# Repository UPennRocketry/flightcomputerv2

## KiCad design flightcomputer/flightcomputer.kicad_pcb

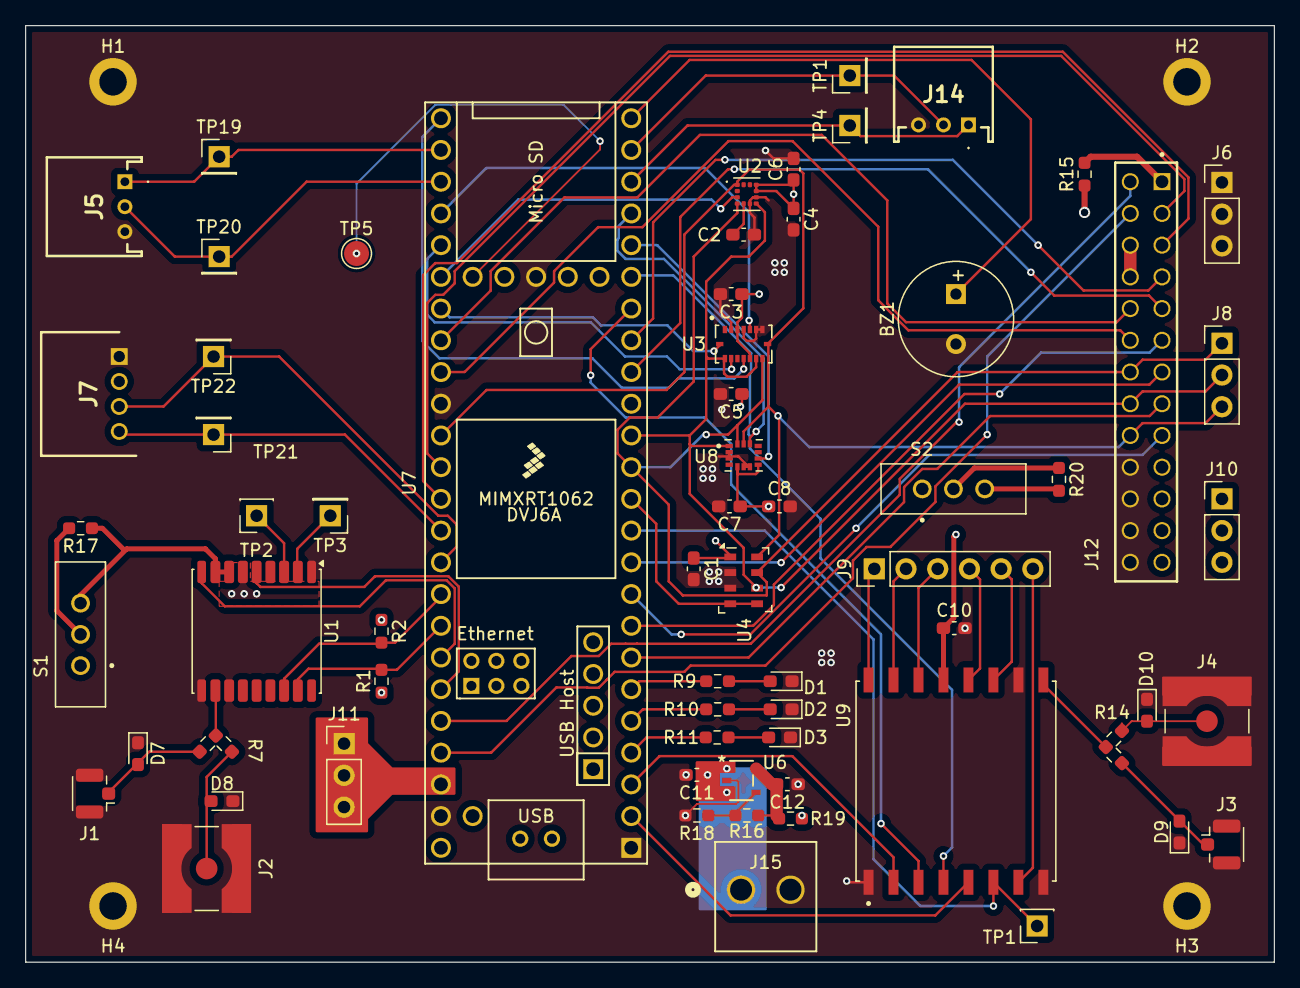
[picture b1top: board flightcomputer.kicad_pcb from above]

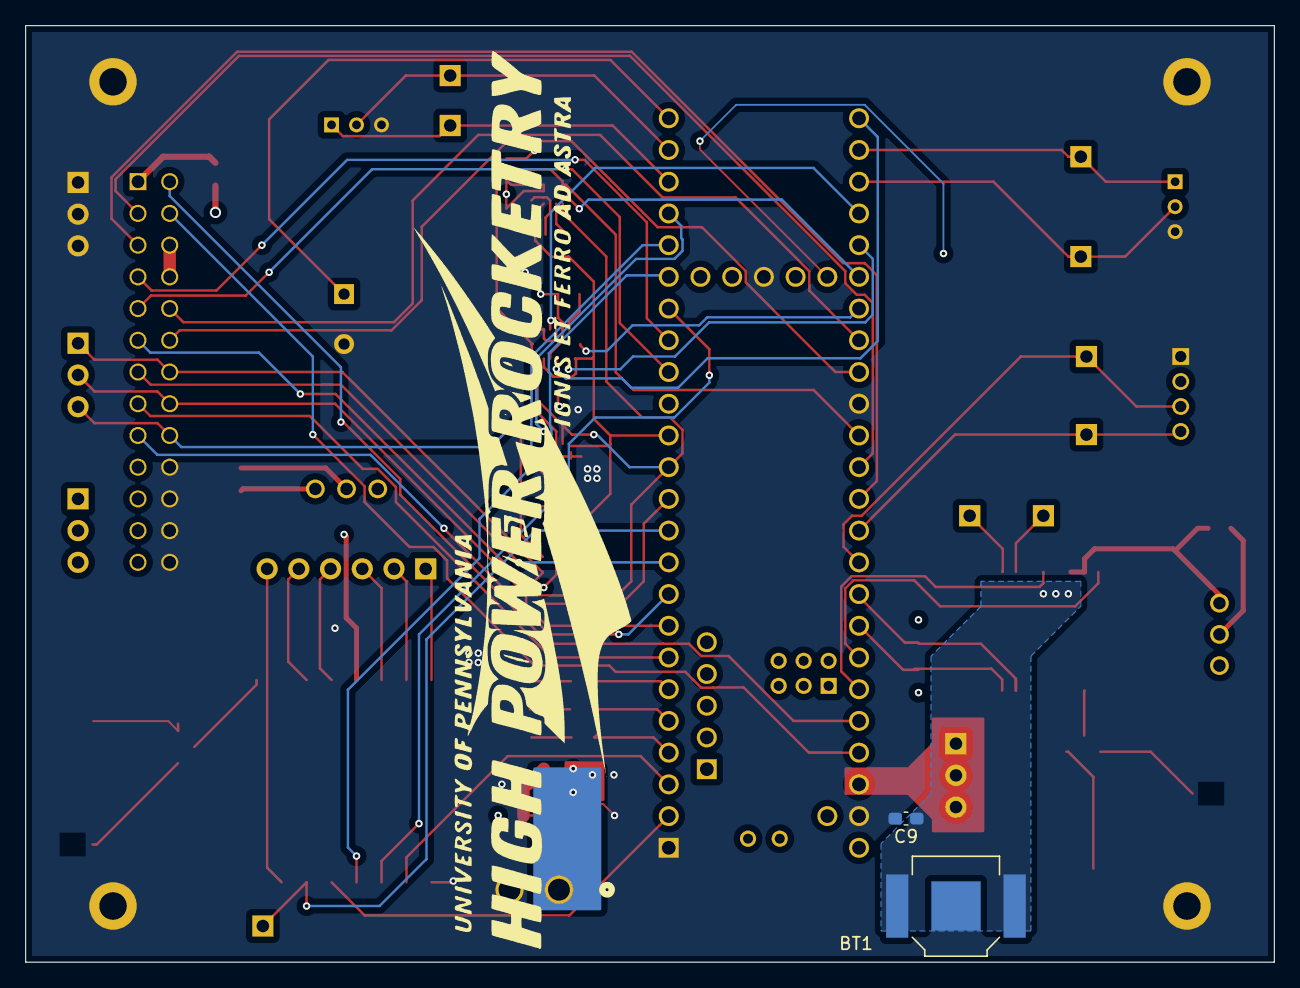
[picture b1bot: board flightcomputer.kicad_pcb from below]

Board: 4 copper layers, 100.0 x 75.0 mm, 72 parts (2 on the bottom side), 72 nets.

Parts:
BT1: 2998TR; BAT_2998TR
BZ1: Buzzer; MagneticBuzzer_PUI_AT-0927-TT-6-R
C1, C3, C5: 0.1uF; C_0603_1608Metric_Pad1.08x0.95mm_HandSolder
C2: 220nF; C_0603_1608Metric_Pad1.08x0.95mm_HandSolder
C4, C7, C8: 100nF; C_0603_1608Metric_Pad1.08x0.95mm_HandSolder
C6, C10: 10uF; C_0603_1608Metric_Pad1.08x0.95mm_HandSolder
C9, C11, C12: 1uF; C_0603_1608Metric_Pad1.08x0.95mm_HandSolder
D1, D2, D3: LED; LED_0603_1608Metric_Pad1.05x0.95mm_HandSolder
D7, D8, D9, D10: ESD9B5.0ST5G; D_0603_1608Metric_Pad1.05x0.95mm_HandSolder
H1, H2, H3, H4: MountingHole_Pad; MountingHole_2.2mm_M2_DIN965_Pad
J1, J3: Conn_Coaxial; U.FL_Hirose_U.FL-R-SMT-1_Vertical
J2, J4: Conn_Coaxial; SMA_Amphenol_132134-10_Vertical
J5, J14: S3B-PH-K-S-GW; S3BPHKSGW
J6, J8, J10, J11: Conn_01x03; PinHeader_1x03_P2.54mm_Vertical
J7: S4B-PH-K-S_LF__SN_
J9: Conn_01x06; PinHeader_1x06_P2.54mm_Vertical
J12: ESQ-113-14-G-D; SAMTEC_ESQ-113-14-G-D
J15: B2P-VHLFSN; CONN_B2P-VH_JST
R1, R2: 4.7k; R_0603_1608Metric_Pad0.98x0.95mm_HandSolder
R7, R14: 0; RES_0OHM_Y
R9, R10, R11: 500; R_0603_1608Metric_Pad0.98x0.95mm_HandSolder
R15, R17, R19, R20: 0; R_0603_1608Metric_Pad0.98x0.95mm_HandSolder
R16: 31.6k; R_0603_1608Metric_Pad0.98x0.95mm_HandSolder
R18: 10k; R_0603_1608Metric_Pad0.98x0.95mm_HandSolder
S1, S2: EG1218; SW_EG1218
TP1, TP3, TP4, TP19, TP20, TP21, TP22: TestPoint; PinHeader_1x01_P2.54mm_Vertical
TP1#2, TP2: TestPoint; PinSocket_1x01_P2.54mm_Vertical
TP5: TestPoint; TestPoint_Pad_D2.0mm
U1: MAX-M10S; ublox_MAX
U2: LIS2MDLTR; PQFN50P200X200X70-12N
U3: BMI088; PQFN50P450X300X100-16N
U4: MS5607-02BA; LGA-8_3x5mm_P1.25mm
U6: NCP718ASNADJT1G; TSOT-23-5_2P9X1P6_ONS-L
U7: Teensy4.1; Teensy41
U8: LSM6DSO32TR; XDCR_LSM6DSO32TR
U9: RFM96W-433S2; MODULE_RFM96W-433S2

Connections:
/5V: J10.1, J10.2, J10.3, J12.19, J12.21, J12.23, J12.25, R19.2, U7.48 (VIN)
/5v_cursns: J12.12, U7.33 (41_A17)
/5v_fault: J12.10, U7.32 (40_A16)
/6v_cursns: J12.04, U7.45 (23_A9_CRX1_MCLK1)
/6v_fault: J12.02, U7.44 (22_A8_CTX1)
/GPS_int: U1.5 (EXTINT), U7.43 (21_A7_RX5_BCLK1)
/GPS_reset: U1.9 (~RESET), U7.42 (20_A6_TX5_LRCLK1)
/GPS_scl: R1.2, U1.17 (SCL), U7.41 (19_A5_SCL)
/GPS_sda: R2.2, U1.16 (SDA), U7.40 (18_A4_SDA)
/LDO_5V: C12.2, R16.2, R19.1, U6.5 (OUT)
/LED1: R9.1, U7.6 (4_BCLK2)
/LED2: R10.1, U7.5 (3_LRCLK2)
/LED3: R11.1, U7.4 (2_OUT2)
/PYRO1: J12.11, U7.8 (6_OUT1D)
/PYRO1CONN: J12.13, U7.10 (8_TX2_IN1)
/PYRO2: J12.15, U7.7 (5_IN2)
/PYRO2CONN: J12.17, U7.9 (7_RX2_OUT1A)
/SENSE_miso: J8.2, J12.16, U2.7 (INT/DRDY/SDO), U3.10 (SDO2), U3.15 (SDO1), U4.6 (SDO), U7.14 (12_MISO_MQSL), U8.1 (SDO/SA0)
/SENSE_mosi: J8.1, J12.14, U2.4 (SDA/SDI/SDO), U3.9 (SDA/SDI), U4.7 (SDI/SDA), U7.13 (11_MOSI_CTX1), U8.14 (SDA)
/SENSE_sck: J8.3, J12.18, U2.1 (SCL/SPC), U3.8 (SCL/SCK), U4.8 (SCLK), U7.35 (13_SCK_LED), U8.13 (SCL)
/V_ext: C11.1, J15.1, U6.1 (IN), U6.3 (EN)
/aux1_scl: J7.4, TP21.1, U7.38 (16_A2_RX4_SCL1)
/aux1_sda: J7.3, TP22.1, U7.39 (17_A3_TX4_SDA1)
/aux8_rx: J5.1, TP19.1, U7.26 (34_RX8)
/aux8_tx: J5.2, TP20.1, U7.27 (35_TX8)
/baro_cs: U4.4 (CSB), U4.5 (CSB), U7.12 (10_CS_MQSR)
/buzz_pwm: BZ1.1 (+), U7.24 (32_OUT1B)
/can_rx: J14.1, TP4.1, U7.22 (30_CRX3)
/can_tx: J14.2, TP1.1, U7.23 (31_CTX3)
/gps_3.3v: R17.1, S1.3, U1.7 (VCC_IO), U1.8 (VCC)
/gps_vbckp: BT1.P1, BT1.P2, C9.1, U1.6 (V_BCKP)
/imu_accel_cs: U3.14 (CSB1), U7.29 (37_CS)
/imu_accel_int1: U3.16 (INT1), U7.31 (39_MISO1_OUT1A)
/imu_gyro_cs: U3.5 (CSB2), U7.28 (36_CS)
/imu_gyro_int1: U3.12 (INT3), U7.25 (33_MCLK2)
/lsmimu_cs: U7.21 (29_TX7), U8.12 (CS)
/lsmimu_int: U7.20 (28_RX7), U8.9 (INT2)
/mag_cs: U2.3 (CS), U7.30 (38_CS1_IN1)
/radio_3.3v: C10.1, R20.2, S2.3, U9.13 (3.3V)
/radio_cs: U7.2 (0_RX1_CRX2_CS1), U9.5 (NSS)
/radio_dio0: J9.6, U9.7 (DIO5)
/radio_dio1: J9.4, U9.12 (DIO4)
/radio_dio2: J9.5, U9.11 (DIO3)
/radio_dio3: J9.1, U9.16 (DIO2)
/radio_dio4: J9.2, U9.15 (DIO1)
/radio_dio5: J9.3, U9.14 (DIO0)
/radio_miso: U7.3 (1_TX1_CTX2_MISO1), U9.2 (MISO)
/radio_mosi: U7.18 (26_A12_MOSI1), U9.3 (MOSI)
/radio_reset: TP1#2.1, U7.11 (9_OUT1C), U9.6 (RESET)
/radio_sck: U7.19 (27_A13_SCK1), U9.4 (SCK)
/servo1_pwm: J12.05, U7.37 (15_A1_RX3_SPDIF_IN)
/servo2_pwm: J12.03, U7.36 (14_A0_TX3_SPDIF_OUT)
/teensy_3.3v: C1.1, C3.1, C4.1, C5.1, C6.1, C7.1, C8.1, J7.2, J11.1, J11.2, J11.3, R1.1, R2.1, R15.1, R17.2, R20.1, S1.2, S2.2, U2.9 (VDD), U2.10 (VDD_IO), U3.3 (VDD), U3.11 (VDDIO), U4.1 (VDD), U7.15 (3V3), U7.46 (3V3), U7.51 (3V3), U8.5 (VDDIO), U8.8 (VDD)
/xV: J12.06, J12.08
/x_cursns: J12.07, U7.17 (25_A11_RX6_SDA2)
/x_fault: J12.09, U7.16 (24_A10_TX6_SCL2)
GND: BT1.N, BZ1.2 (-), C1.2, C2.2, C3.2, C4.2, C5.2, C6.2, C7.2, C8.2, C9.2, C10.2, C11.2, C12.1, D1.1 (K), D2.1 (K), D3.1 (K), D7.1 (A1), D8.1 (A1), D9.1 (A1), D10.1 (A1), H1.1, H2.1, H3.1, H4.1, J1.2 (Ext), J2.2 (Ext), J3.2 (Ext), J4.2 (Ext), J5.3, J6.1, J6.2, J6.3, J7.1, J12.20, J12.22, J12.24, J12.26, J14.3, J15.2, R18.2, U1.1 (GND), U1.10 (GND), U1.12 (GND), U2.6 (GND), U2.8 (GND__1), U3.2 (NC), U3.4 (GNDA), U3.6 (GNDIO), U3.7 (PS), U4.2 (PS), U4.3 (GND), U6.2 (GND), U7.1 (GND), U7.34 (GND), U7.47 (GND), U7.52 (GND), U8.2 (SDX), U8.3 (SCX), U8.6 (GND), U8.7 (GND__1), U9.1 (GND), U9.8 (GND), U9.10 (GND)
unnamed: D1.2 (A), R9.2
unnamed: D2.2 (A), R10.2
unnamed: D3.2 (A), R11.2
unnamed: D7.2 (A2), J1.1 (In), R7.3
unnamed: D8.2 (A2), J2.1 (In), R7.2
unnamed: D9.2 (A2), J3.1 (In), R14.3
unnamed: D10.2 (A2), J4.1 (In), R14.2
unnamed: J12.01, R15.2
unnamed: R7.1, U1.11 (RF_IN)
unnamed: TP2.1, U1.3 (RXD)
unnamed: TP3.1, U1.2 (TXD)
unnamed: C2.1, U2.5 (C1)
unnamed: R16.1, R18.1, U6.4 (NC/ADJ)
unnamed: TP5.1, U7.54 (ON_OFF)
unnamed: R14.1, U9.9 (ANT)

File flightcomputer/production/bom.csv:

Designator,Footprint,Quantity,Value,LCSC Part #
BT1,BAT_2998TR,1,2998TR,
BZ1,MagneticBuzzer_PUI_AT-0927-TT-6-R,1,Buzzer,AT-0927-TT-6-R
"C1, C3, C5",0603,3,0.1uF,
"C10, C6",0603,2,10uF,
C2,0603,1,220nF,
"C4, C7, C8",0603,3,100nF,
C9,0603,1,1uF,
"D1, D2, D3",0603,3,LED,
"D10, D7, D8, D9",0603,4,ESD9B5.0ST5G,
"J1, J3",U.FL_Hirose_U.FL-R-SMT-1_Vertical,2,Conn_Coaxial,
J12,SAMTEC_ESQ-113-14-G-D,1,ESQ-113-14-G-D,
"J14, J5",S3BPHKSGW,2,S3B-PH-K-S-GW,
"J2, J4",SMA_Amphenol_132134-10_Vertical,2,Conn_Coaxial,132134
J7,S4B-PH-K-S_LF__SN_,1,S4B-PH-K-S_LF__SN_,
"R1, R2",0603,2,4.7k,
"R10, R11, R9",0603,3,500,
R15,0603,1,0,
S1,SW_EG1218,1,EG1218,
"TP1_2, TP19, TP20, TP21, TP22, TP3, TP4",PinHeader_1x01_P2.54mm_Vertical,7,TestPoint,
"TP1, TP2",PinSocket_1x01_P2.54mm_Vertical,2,TestPoint,
U1,ublox_MAX,1,MAX-M10S,MAX-M10S-00B
U2,PQFN50P200X200X70-12N,1,LIS2MDLTR,
U3,PQFN50P450X300X100-16N,1,BMI088,BMI088
U4,LGA-8_3x5mm_P1.25mm,1,MS5607-02BA,MS560702BA03-50
U7,Teensy41,1,Teensy4.1,
U8,XDCR_LSM6DSO32TR,1,LSM6DSO32TR,
U9,MODULE_RFM96W-433S2,1,RFM96W-433S2,

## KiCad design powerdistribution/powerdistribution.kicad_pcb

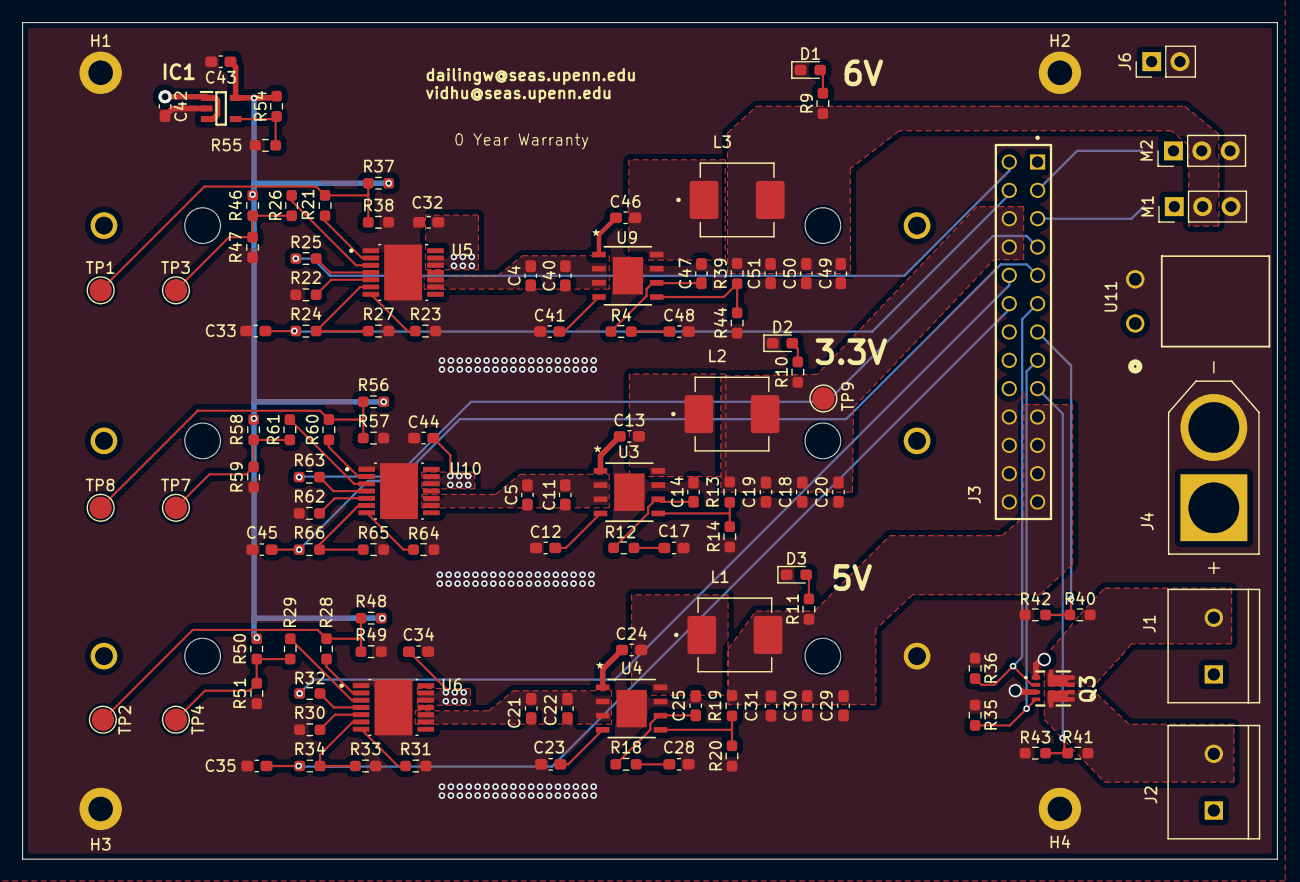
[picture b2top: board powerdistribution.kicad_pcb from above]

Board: 4 copper layers, 112.5 x 75.0 mm, 122 parts (1 on the bottom side), 71 nets.

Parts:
BT1: BK-18650-PC6; BAT_BK-18650-PC6
C4, C5, C11, C21, C22, C40: 10uf; C_0603_1608Metric_Pad1.08x0.95mm_HandSolder
C12, C23, C41: 10nf; C_0603_1608Metric_Pad1.08x0.95mm_HandSolder
C13, C24, C46: 100nF; C_0603_1608Metric_Pad1.08x0.95mm_HandSolder
C14, C25, C47: 33pf; C_0603_1608Metric_Pad1.08x0.95mm_HandSolder
C17, C28, C48: 2.7nf; C_0603_1608Metric_Pad1.08x0.95mm_HandSolder
C18, C19, C29, C30, C49, C50: 22 uf; C_0603_1608Metric_Pad1.08x0.95mm_HandSolder
C20, C31, C51: 22uf; C_0603_1608Metric_Pad1.08x0.95mm_HandSolder
C32, C33, C34, C35, C44, C45: 220nf; C_0603_1608Metric_Pad1.08x0.95mm_HandSolder
C42, C43: 1uF; C_0603_1608Metric_Pad1.08x0.95mm_HandSolder
D1, D2, D3: LED; LED_0603_1608Metric_Pad1.05x0.95mm_HandSolder
H1, H2, H3, H4: MountingHole_Pad; MountingHole_2.2mm_M2_DIN965_Pad
IC1: NCP718ASNADJT1G; NCP718_SOT95P280X100-5N
J1, J2: 282837-2; TE_282837-2
J3: ESQ-113-12-G-D; SAMTEC_ESQ-113-12-G-D
J4: XT60-M; AMASS_XT60-M
J6: Conn_01x02; PinHeader_1x02_P2.54mm_Vertical
L1, L3: CSAB0730-4R7M
L2: CSAB0730-3R3M
M1, M2: Motor_Servo; PinHeader_1x03_P2.54mm_Vertical
Q3: SI7232DN-T1-GE3; SI7232DNT1GE3
R4, R12, R18: 10.5k; R_0603_1608Metric_Pad0.98x0.95mm_HandSolder
R9, R10, R11: R; R_0603_1608Metric_Pad0.98x0.95mm_HandSolder
R13: 31.6k; R_0603_1608Metric_Pad0.98x0.95mm_HandSolder
R14, R20, R23, R31, R35, R36, R37, R38, R44, R46, R47, R48, R49, R50, R51, R56, R57, R58, R59, R64: 10k; R_0603_1608Metric_Pad0.98x0.95mm_HandSolder
R19: 52.3k; R_0603_1608Metric_Pad0.98x0.95mm_HandSolder
R21, R22, R24, R25, R26, R28, R29, R30, R32, R34, R60, R61, R62, R63, R66: 5k; R_0603_1608Metric_Pad0.98x0.95mm_HandSolder
R27, R33, R65: 1k; R_0603_1608Metric_Pad0.98x0.95mm_HandSolder
R39: 65k; R_0603_1608Metric_Pad0.98x0.95mm_HandSolder
R40, R41: 20k; R_0603_1608Metric_Pad0.98x0.95mm_HandSolder
R42, R43: 10K; R_0603_1608Metric_Pad0.98x0.95mm_HandSolder
R54: 19k; R_0603_1608Metric_Pad0.98x0.95mm_HandSolder
R55: 6k; R_0603_1608Metric_Pad0.98x0.95mm_HandSolder
TP1, TP2, TP3, TP4, TP7, TP8, TP9: TestPoint; TestPoint_Pad_D2.0mm
U3, U4, U9: AP64501QSP-13; SO-8EP_DIO-L
U5, U6, U10: TPS1HC30BQPWPRQ1; IC_TPS1HC30BQPWPRQ1
U11: S2P-VH; S2P-VH_JST

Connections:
/3.3V: C18.1, C19.1, C20.1, J3.06, J3.08, L2.2, R10.1, R13.1, TP9.1
/3.3V_DIAGEN: R58.1, R59.2, R61.1, TP7.1
/3.3V_EN: R56.1, R57.2, R60.1, TP8.1
/3.3V_LIN: C13.2, L2.1, U3.8 (SW)
/3.3V_SWout: C5.2, C11.2, U3.2 (VIN), U3.3 (EN), U10.9 (VOUT), U10.10 (VOUT__1)
/3.3v_cursns: C45.2, J3.09, R66.2
/3.3v_fault: J3.07, R63.2
/5V: C29.1, C30.1, C31.1, J3.19, J3.21, J3.23, J3.25, L1.2, R11.1, R19.1
/5V_DIAGEN: R29.1, R50.1, R51.2, TP4.1
/5V_EN: R28.1, R48.1, R49.2, TP2.1
/5V_LIN: C24.2, L1.1, U4.8 (SW)
/5V_SWout: C21.2, C22.2, U4.2 (VIN), U4.3 (EN), U6.9 (VOUT), U6.10 (VOUT__1)
/5v_cursns: C35.2, J3.12, R34.2
/5v_fault: J3.10, R32.2
/6V: C49.1, C50.1, C51.1, L3.2, M1.2 (+), M2.2 (+), R9.1, R39.1
/6V_DIAGEN: R26.1, R46.1, R47.2, TP3.1
/6V_EN: R21.1, R37.1, R38.2, TP1.1
/6V_LIN: C46.2, L3.1, U9.8 (SW)
/6V_SWout: C4.2, C40.2, U5.9 (VOUT), U5.10 (VOUT__1), U9.2 (VIN), U9.3 (EN)
/6v_cursns: C33.2, J3.04, R24.2
/6v_fault: J3.02, R25.2
/B1: BT1.1+, BT1.2-
/B2: BT1.2+, BT1.3-
/LDO_5V: C43.1, IC1.5 (OUT), R37.2, R46.2, R48.2, R50.2, R54.2, R56.2, R58.2
/PYRO1: J3.11, Q3.2 (G1), R36.2
/PYRO1CONN: J3.13, R40.1, R42.1
/PYRO2: J3.15, Q3.4 (G2), R35.2
/PYRO2CONN: J3.17, R41.1, R43.1
/PYROOUT1: J1.2, Q3.7 (D1_1), Q3.8 (D1_2), Q3.9 (D1_3), Q3.10 (D1_4), Q3.11 (D1_5), Q3.15 (D1_6), R40.2
/PYROOUT2: J2.2, Q3.5 (D2_1), Q3.6 (D2_2), Q3.12 (D2_3), Q3.13 (D2_4), Q3.14 (D2_5), Q3.16 (D2_6), R41.2
/Pack+: BT1.3+, C32.2, C34.2, C42.1, C44.2, IC1.1 (IN), IC1.3 (EN), J1.1, J2.1, J4.P (POS), J6.1, U5.12 (VBB), U5.13 (VBB__1), U6.12 (VBB), U6.13 (VBB__1), U10.12 (VBB), U10.13 (VBB__1), U11.1
/servo1_pwm: J3.05, M1.1 (PWM)
/servo2_pwm: J3.03, M2.1 (PWM)
GND: BT1.1-, C4.1, C5.1, C11.1, C12.1, C14.2, C17.2, C18.2, C19.2, C20.2, C21.1, C22.1, C23.1, C25.2, C28.2, C29.2, C30.2, C31.2, C32.1, C33.1, C34.1, C35.1, C40.1, C41.1, C42.2, C43.2, C44.1, C45.1, C47.2, C48.2, C49.2, C50.2, C51.2, D1.1 (K), D2.1 (K), D3.1 (K), H1.1, H2.1, H3.1, H4.1, IC1.2 (GND), J3.20, J3.22, J3.24, J3.26, J4.N (NEG), J6.2, M1.3 (-), M2.3 (-), Q3.1 (S1), Q3.3 (S2), R14.1, R20.1, R22.1, R23.2, R27.1, R30.1, R31.2, R33.1, R35.1, R36.1, R38.1, R42.2, R43.2, R44.1, R47.1, R49.1, R51.1, R55.1, R57.1, R59.1, R62.1, R64.2, R65.1, U3.7 (GND), U3.EPAD (EXPOSED_PAD), U4.7 (GND), U4.EPAD (EXPOSED_PAD), U5.1 (GND), U5.15 (EXP), U6.1 (GND), U6.15 (EXP), U9.7 (GND), U9.EPAD (EXPOSED_PAD), U10.1 (GND), U10.15 (EXP), U11.2
unnamed: C17.1, R12.2
unnamed: C28.1, R18.2
unnamed: C48.1, R4.2
unnamed: D1.2 (A), R9.2
unnamed: D2.2 (A), R10.2
unnamed: D3.2 (A), R11.2
unnamed: IC1.4 (NC/ADJ), R54.1, R55.2
unnamed: C13.1, U3.1 (BST)
unnamed: C14.1, R12.1, U3.6 (COMP)
unnamed: R13.2, R14.2, U3.5 (FB)
unnamed: C12.2, U3.4 (SS)
unnamed: C24.1, U4.1 (BST)
unnamed: C25.1, R18.1, U4.6 (COMP)
unnamed: R19.2, R20.2, U4.5 (FB)
unnamed: C23.2, U4.4 (SS)
unnamed: R26.2, U5.3 (DIAG_EN)
unnamed: R21.2, U5.2 (EN)
unnamed: R23.1, U5.7 (ILIM)
unnamed: R22.2, U5.5 (LATCH)
unnamed: R24.1, R27.2, U5.6 (SNS)
unnamed: R25.1, U5.4 (~FAULT)
unnamed: R29.2, U6.3 (DIAG_EN)
unnamed: R28.2, U6.2 (EN)
unnamed: R31.1, U6.7 (ILIM)
unnamed: R30.2, U6.5 (LATCH)
unnamed: R33.2, R34.1, U6.6 (SNS)
unnamed: R32.1, U6.4 (~FAULT)
unnamed: C46.1, U9.1 (BST)
unnamed: C47.1, R4.1, U9.6 (COMP)
unnamed: R39.2, R44.2, U9.5 (FB)
unnamed: C41.2, U9.4 (SS)
unnamed: R61.2, U10.3 (DIAG_EN)
unnamed: R60.2, U10.2 (EN)
unnamed: R64.1, U10.7 (ILIM)
unnamed: R62.2, U10.5 (LATCH)
unnamed: R65.2, R66.1, U10.6 (SNS)
unnamed: R63.1, U10.4 (~FAULT)

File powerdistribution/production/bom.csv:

Designator,Footprint,Quantity,Value,LCSC Part #
BT1,BAT_BK-18650-PC6,1,BK-18650-PC6,
"C21, C22, C4, C40",0603,4,10uf,
"C23, C41",0603,2,10nf,
"C24, C46",0603,2,100nF,
"C28, C48",0603,2,2.7nf,
"C29, C30, C49, C50",0603,4,22 uf,
"C31, C51",0603,2,22uf,
"C32, C33, C34, C35",0603,4,220nf,
"C42, C43",0603,2,1uF,
"D1, D2, D3",0603,3,LED,
IC1,NCP718_SOT95P280X100-5N,1,NCP718ASNADJT1G,
"J1, J2",TE_282837-2,2,282837-2,
J3,SAMTEC_ESQ-113-12-G-D,1,ESQ-113-12-G-D,
J4,AMASS_XT60-M,1,XT60-M,
J6,PinHeader_1x02_P2.54mm_Vertical,1,Conn_01x02,
"L1, L3",CSAB0730-4R7M,2,CSAB0730-4R7M,
L2,CSAB0730-3R3M,1,CSAB0730-3R3M,
Q3,SI7232DNT1GE3,1,SI7232DN-T1-GE3,
"R10, R11, R9",0603,3,R,
"R18, R4",0603,2,10.5k,
R19,0603,1,52.3k,
"R20, R23, R31, R35, R36, R38, R42, R43, R44, R47, R49, R51",0603,12,10k,
"R21, R24, R25, R26, R28, R29, R32, R34",0603,8,5k,
"R27, R33",0603,2,1k,
R39,0603,1,65k,
"R40, R41",0603,2,20k,
R54,0603,1,19k,
R55,0603,1,6k,
"TP1, TP2, TP3, TP4, TP9",TestPoint_Pad_D2.0mm,5,TestPoint,
U11,S2P-VH_JST,1,S2P-VH,
"U4, U9",SO-8EP_DIO-L,2,AP64501QSP-13,
"U5, U6",IC_TPS1HC30BQPWPRQ1,2,TPS1HC30BQPWPRQ1,

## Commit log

2025-10-05 initial projects
2025-10-14 all boards
2025-11-02 no esp32, may add
2025-11-02 pwrdist draft
2025-11-04 BMS draft
2025-11-09 pwr draft
2025-11-09 gps and radio additions
2025-11-11 efuse draft
2025-11-11 added ports and test points
2025-11-16 small update
2025-11-16 efuse and bms pcb draft
2025-11-17 draft
2025-11-18 added buck converters into schematic
2025-11-18 placement
2025-11-20 organization, still schematic errors
2025-11-20 minor change
2025-11-20 swapped pyro transistors for same ones on bms
2025-11-23 add models
2025-12-01 Y 0ohm for antenna selection
2025-12-07 bms parts
2025-12-07 bms parts2
2025-12-29 buck fixes and new components
2026-01-09 high side switch
2026-01-14 reorganization, need to update pyros, reconsider charging, assign nets to pins, think how pin switch will be mounted
2026-01-15 power should be ok now? need to look at BMS, pyro, connectors, remaining nets..
2026-01-18 power placement start
2026-02-01 placement draft 1
2026-02-01 updated pyro
2026-02-15 dnp 12v buck, some notes
2026-02-15 update bms parts + board size
2026-02-15 nuked placement, will update
2026-02-17 update bms to 3 battery
2026-02-22 pwr board general placement
2026-02-22 fc new connector
2026-02-22 connector nets
2026-03-01 new board size+routing
2026-03-01 resize
2026-03-03 pd placement
2026-03-07 flight computer routing
2026-03-15 fc checkpoint
2026-03-15 starting new placement
2026-03-16 power board placed and routed except connector, increased board length by 5mm
2026-03-16 clean up, aligning connectors and board coordinates between fc and power board
2026-03-17 pd placement finish
2026-03-18 hole+connector alignment finish, fc signal routing finish, fc drc warnings related to footprints/silkscreen
2026-03-21 killed BMS, updated pyro fets with lower resistance, updated inductor, replace + reroute, fixed some DRC in flight computer (dont know why remaining are being caused, hopefully jlc doesnt care), next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
2026-03-22 fixed fc silkscreen drc + added hpr logo, coax violation seems intentional so can be ignored, jlc says tolerance 0.127 so 0.13mm should be fine
2026-03-22 generate production files, fix remaining pd silkscreen drc, ignored fc coax violations, also the actual pad distance is defo 0.15mm so it should be fine, all drc pass 👍
2026-03-22 changed coax diodes to 0603, reconfigure conn to add 3.3v, added indicator LEDs.
2026-03-23 power board silks
2026-03-23 production files
2026-03-29 schematic notes and placement revisions for order
2026-04-26 fixes
2026-04-26 add jst 2pin for 5V fc
2026-04-26 use vert jst
2026-04-26 add LDO fc
2026-04-26 add on/off test pad
2026-04-27 prod files
2026-04-29 final fixes
